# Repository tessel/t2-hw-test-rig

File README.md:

# t2-hw-test-rig

KiCAD design files for test rigs for Technical Machine's Tessel 2

To download [TM's KiCAD library](https://github.com/technicalmachine/tm-kicad-library), containing all the schematic symbols and footprints, run this command:

```
git submodule update --init
```

## Notes

* We use the daily builds of KiCAD (for [Ubuntu](https://code.launchpad.net/~js-reynaud/+archive/ubuntu/ppa-kicad and [OS X](http://www.kicad-pcb.org/display/KICAD/Installing+KiCad#InstallingKiCad-MacOSX) ) and you should too!
* As a general rule, do not assume that schematic, layout, and manufacturig exports were kept abreast on each commit. Do a fresh export (or use tagged releases) if you intend to actually send off gerbers.

### Troubleshooting

**No components rendered in 3D viewer (OS X):** You may need to change the environment variable for the 3D model path. Run this command and reset KiCad; this fix will work for the duration of your logged in session on the computer:

```
launchctl setenv KISYS3DMOD "/Library/Application Support/kicad/packages3d"
```

## Mechanical Model

Our [physical CAD model](https://cad.onshape.com/documents/50a5c011c1d44d7ca5c90fbf) is available on [OnShape](http://onshape.com), a cloud-based 3D CAD system that is free for public projects. It supports export in a variety of formats to other 3D CAD tools.

## License

CC-BY-SA and/or Solderpad at your option except where otherwise noted.

See `license.txt`.

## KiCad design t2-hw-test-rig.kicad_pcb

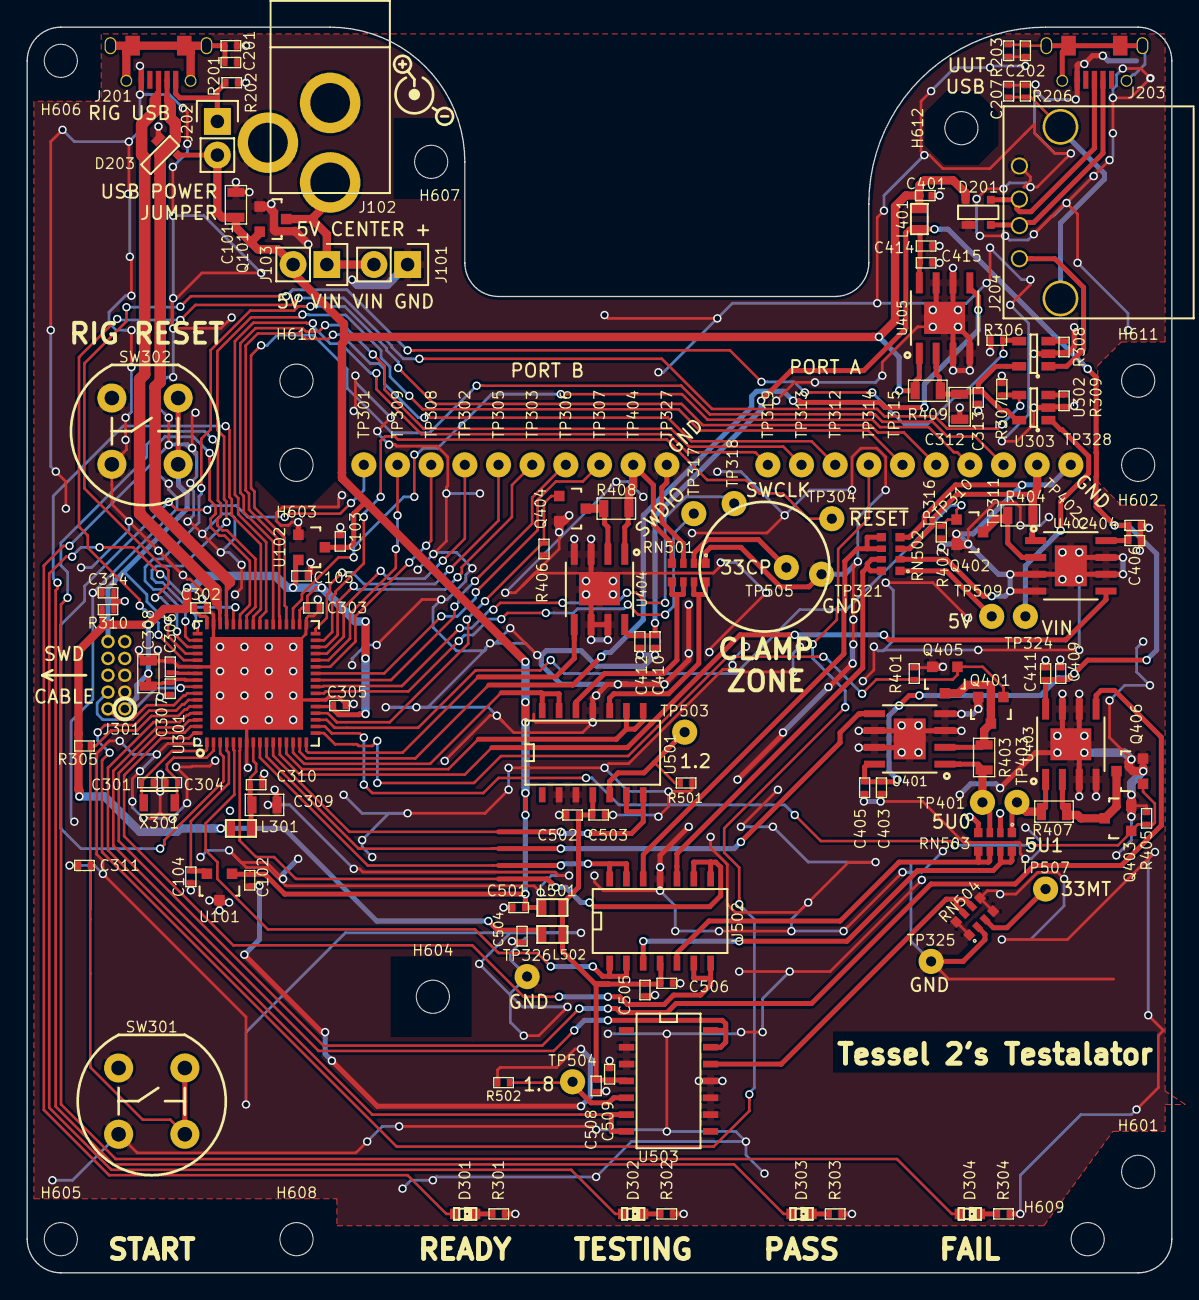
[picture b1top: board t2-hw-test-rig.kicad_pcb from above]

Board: 2 copper layers, 86.4 x 94.0 mm, 157 parts (0 on the bottom side), 95 nets.

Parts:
C101, C308, C309, C312: 10uF; SMD-0805-C
C102, C103, C104, C105, C302, C303, C305, C307, C310, C311, C313, C314, C401, C403, C404, C409, C410, C414, C502, C504, C505, C508: 100nF; SMD-0402-C
C201, C202, C207, C405, C406, C411, C412, C415, C503, C506, C509: 100pF; SMD-0402-C
C301, C304: 10pF; SMD-0402-C
C306: 1uF; SMD-0402-C
C501: 100nF DNP; SMD-0402-C
D201, D203: PRTR5V0U2X,215
D301: BLUE; LED-0603
D302: YELLOW; LED-0603
D303: GREEN; LED-0603
D304: RED; LED-0603
H601, H602, H603, H604, H605, H606, H607, H608, H609, H610, H611, H612: M2.5; MountingHole_2-5mm
J101, J103, J202: CONN_01X02; Pin_Header_Straight_1x02
J102: BARREL_JACK
J201, J203: MICROUSB-TH; Seeed-USB-Micro-320010028
J204: USB_A_TH; USB-A
J301: CONN_02x05, 0.05"; CONN_02x05_0.05in
L301, L401, L502: 10uH; SMD-0603-R
L501: 10uH DNP; SMD-0603-R
Q101: pMOS; SOT-23
Q401, Q402, Q403, Q404: CJ2302; SOT-23
Q405, Q406: CJ2302 DNP; SOT-23
R201, R202, R203, R206: 100kR; SMD-0402-R
R301, R304, R308, R309: 1kR; SMD-0402-R
R302: 330R; SMD-0402-R
R303: 120R; SMD-0402-R
R305, R306, R307, R310, R401, R402, R405, R406, R501, R502: 10kR; SMD-0402-R
R403, R404, R407, R408, R409: 20mR 1%; SMD-0805-R
RN501, RN502, RN503, RN504: ACASA100221002P100; ACAS0612
SW301, SW302: Switch_DPST; SPST-TH
TP301, TP302, TP303, TP304, TP305, TP306, TP307, TP308, TP309, TP310, TP311, TP312, TP313, TP314, TP315, TP316, TP317, TP318, TP319, TP321, TP324, TP325, TP326, TP327, TP328, TP401, TP402, TP403, TP404, TP503, TP504, TP505, TP507, TP509: 0932-0-15-20-77-14-11-0
U101: MAX6102; SOT-23
U102: XC6206P332MR-G; SOT-23
U301: ATSAMD21J18A-MUT; QFN-64-1EP_9x9x0.5-8MILDRC
U302, U303: AAT4610; SOT-23-5
U401, U402, U403, U404, U405: MAX9919FASA+; SOIC-8-N-1EP
U501, U502, U503: TSV324IDT; SOIC-14_N
X301: FC-135

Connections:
5VUSB0_DIV_BUFF: U301.64, U502.6, U502.7
5VUSB1_DIV_BUFF: U301.5, U502.1, U502.2
5V_DIV_BUFF: U301.6, U502.8, U502.9
12_BUFF: U301.11, U501.6, U501.7
18_BUFF: U301.61, U503.6, U503.7
33CP_DIV_BUFF: U301.13, U501.8, U501.9
33MT_DIV_BUFF: U301.62, U503.13, U503.14
33PA_DIV_BUFF: U301.9, U502.13, U502.14
33PB_DIV_BUFF: U301.14, U501.13, U501.14
+3V3: C105.1, C302.1, C303.1, C305.1, C307.1, C308.1, C504.1, J301.1, L301.1, L502.2, R305.2, R310.2, U102.2, U301.21, U301.34, U301.48, U301.56
+5V: C101.1, C102.1, C103.1, C401.1, C501.1, D201.4, D203.4, J103.2, J202.2, L401.2, L501.2, Q101.2, R409.1, U101.1, U102.3, U405.1
/CURRENT/5VUSB0_RS-: Q401.3, Q405.3, R403.2, U401.2
/CURRENT/5VUSB1_RS-: Q403.3, Q406.3, R407.2, U403.2
/CURRENT/33PA_RS-: Q402.3, R404.2, U402.2
/CURRENT/33PB_RS-: Q404.3, R408.2, U404.2
/CURRENT/VCC_CSA: C403.1, C404.1, C405.1, C406.1, C409.1, C410.1, C411.1, C412.1, C414.1, C415.1, L401.1, U401.8, U402.8, U403.8, U404.8, U405.8
/OP AMPS/5VUSB0_DIV: RN503.5, RN503.6, U502.5
/OP AMPS/5VUSB1_DIV: RN503.7, RN503.8, U502.3
/OP AMPS/5V_DIV: RN502.7, RN502.8, U502.10
/OP AMPS/33CP_DIV: RN501.7, RN501.8, U501.10
/OP AMPS/33MT_DIV: RN504.6, RN504.7, U503.12
/OP AMPS/33PA_DIV: RN502.5, RN502.6, U502.12
/OP AMPS/33PB_DIV: RN501.5, RN501.6, U501.12
/OP AMPS/UUT_12: R501.1, TP503.~, U501.5
/OP AMPS/UUT_18: R502.1, TP504.~, U503.5
/OP AMPS/VDD_OPAMPS: C502.1, C503.1, C505.1, C506.1, C508.1, C509.1, L501.1, L502.1, U501.4, U502.4, U503.4
/SAM/FAIL_LED: D304.2, U301.42
/SAM/FAIL_MID: D304.1, R304.2
/SAM/PASS_LED: D303.2, U301.41
/SAM/PASS_MID: D303.1, R303.2
/SAM/PORT_A_G1/TX: TP312.~, U301.37
/SAM/PORT_A_G2/RX: TP313.~, U301.38
/SAM/PORT_A_G3: TP319.~, U301.40
/SAM/PORT_A_MISO: TP315.~, U301.49
/SAM/PORT_A_MOSI: TP314.~, U301.59
/SAM/PORT_A_SCK: TP316.~, U301.50
/SAM/PORT_A_SCL: TP311.~, U301.36
/SAM/PORT_A_SDA: TP310.~, U301.35
/SAM/PORT_B_G1/TX: TP308.~, U301.27
/SAM/PORT_B_G2/RX: TP309.~, U301.28
/SAM/PORT_B_G3: TP301.~, U301.3
/SAM/PORT_B_MISO: TP305.~, U301.32
/SAM/PORT_B_MOSI: TP302.~, U301.29
/SAM/PORT_B_SCK: TP303.~, U301.30
/SAM/PORT_B_SCL: TP307.~, U301.26
/SAM/PORT_B_SDA: TP306.~, U301.25
/SAM/READY_LED: D301.2, U301.43
/SAM/READY_MID: D301.1, R301.2
/SAM/SAM_XTAL32_1: C301.1, U301.1, X301.1
/SAM/SAM_XTAL32_2: C304.1, U301.2, X301.2
/SAM/TEST_IN_PROGRESS_LED: D302.2, U301.44
/SAM/TEST_START_BUTTON: C311.1, R305.1, SW301.2, SW301.4, U301.60
/SAM/TIP_MID: D302.1, R302.2
/SAM/UUT_SWCLK: TP318.~, U301.24
/SAM/UUT_SWDIO: TP317.~, U301.23
/SAM/UUT_VIN: TP324.~, U303.1
/SAM/UUT_~ENABLE~_USB: R306.2, U301.51, U302.4
/SAM/UUT_~ENABLE~_VIN: R307.2, U301.53, U303.4
/SAM/UUT_~RESET: TP304.~, U301.31
/SAM/VDDCORE: C306.1, U301.55
/USB/SAM_USB_SHELL: C201.1, J201.6, J201.7, J201.8, J201.9, J201.10, J201.11, R201.1
/USB/UUT_USB_D+: D201.3, J203.3, J204.3
/USB/UUT_USB_D-: D201.2, J203.2, J204.2
/USB/UUT_USB_PASSTHROUGH_SHELL: C202.1, J203.6, J203.7, J203.8, J203.9, J203.10, J203.11, R203.1
/USB/UUT_USB_SHELL: C207.1, J204.5, J204.6, R206.1
/USB/V_USB_IN: J201.1, J202.1, R202.1
/V_IN: J101.2, J102.1, J103.1, Q101.3
CP_VDDANA: C309.1, C310.1, L301.2, U301.8
GND: C101.2, C102.2, C103.2, C104.2, C105.2, C201.2, C202.2, C207.2, C301.2, C302.2, C303.2, C304.2, C305.2, C306.2, C307.2, C308.2, C309.2, C310.2, C311.2, C312.2, C313.2, C314.2, C401.2, C403.2, C404.2, C405.2, C406.2, C409.2, C410.2, C411.2, C412.2, C414.2, C415.2, C501.2, C502.2, C503.2, C504.2, C505.2, C506.2, C508.2, C509.2, D201.1, D203.1, J101.1, J102.2, J102.3, J201.5, J203.5, J204.4, J301.3, J301.5, Q101.1, Q401.2, Q402.2, Q403.2, Q404.2, Q405.2, Q406.2, R201.2, R202.2, R203.2, R206.2, R301.1, R302.1, R303.1, R304.1, R306.1, R307.1, R308.1, R309.1, R401.2, R402.2, R405.2, R406.2, R501.2, R502.2, RN501.1, RN501.3, RN502.2, RN502.4, RN503.2, RN503.4, RN504.1, RN504.2, RN504.4, RN504.5, RN504.8, SW301.1, SW301.3, SW302.1, SW302.3, TP321.~, TP325.~, TP326.~, TP327.~, TP328.~, U101.3, U102.1, U301.7, U301.22, U301.33, U301.47, U301.54, U301.65, U302.2, U303.2, U401.3, U401.4, U401.6, U401.7, U401.9, U402.3, U402.4, U402.6, U402.7, U402.9, U403.3, U403.4, U403.6, U403.7, U403.9, U404.3, U404.4, U404.6, U404.7, U404.9, U405.3, U405.4, U405.6, U405.7, U405.9, U501.2, U501.3, U501.11, U502.11, U503.2, U503.3, U503.9, U503.10, U503.11
I_PA33: U301.12, U402.5
I_PB33: U301.16, U404.5
I_USB0: U301.10, U401.5
I_USB1: U301.63, U403.5
I_UUT: U301.15, U405.5
unnamed: R308.2, U302.3
unnamed: R309.2, U303.3
PA33_SHORT: Q402.1, R402.1, U301.19
PB33_SHORT: Q404.1, R406.1, U301.20
SAM_USB_D+: D203.2, J201.3, U301.46
SAM_USB_D-: D203.3, J201.2, U301.45
SAM_~RESET: C314.1, J301.10, R310.1, SW302.2, SW302.4, U301.52
SWCLK: J301.4, U301.57
SWDIO: J301.2, U301.58
USB0_SHORT: Q401.1, Q405.1, R401.1, U301.17
USB1_SHORT: Q403.1, Q406.1, R405.1, U301.18
UUT_5V: RN502.1, TP509.~
UUT_5VUSB0: R403.1, RN503.3, TP401.~, U401.1
UUT_5VUSB1: R407.1, RN503.1, TP403.~, U403.1
UUT_5V_UPSTREAM: C312.1, C313.1, R409.2, U302.5, U303.5, U405.2
UUT_33CP: RN501.2, TP505.~
UUT_33MT: RN504.3, TP507.~
UUT_33PA: R404.1, RN502.3, TP402.~, U402.1
UUT_33PB: R408.1, RN501.4, TP404.~, U404.1
UUT_VINUSB: J204.1, U302.1
V_REF: C104.1, U101.2, U301.4

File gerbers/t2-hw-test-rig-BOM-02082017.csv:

,Title,Tessel 2 Test Rig,,,
,Revision,,,,
,Date,Thu 30 Apr 2015,,,
,Generated,Monday, May 30, 2016 'PMt' 12:41:19 PM,
,Company,Technical Machine, Inc.,,
,Comment 1,Copyright 2015,,,
,Comment 2,CC-BY-SA and/or Solderpad at your option ,,,
,Comment 3,,,,
,Comment 4,,,,
,Total Parts,198,,,
,Total Unique Parts,49,,,
,Ref,Qty,Value,Footprint,
,C104 C102 C103 C105 C310 C305 C307 C303 C302 C313 C311 C314 C401 C403 C409 C410 C404 C414 C505 C502 C508 C504 ,22,100nF,SMD-0402,
,C101 C308 C309 C312 ,4,10uF,SMD-0402,
,C201 C207 C202 C405 C411 C412 C406 C415 C503 C506 C509 ,11,100pF,SMD-0402,
,C304 C301 ,2,10pF,SMD-0402,
,C306 ,1,1uF,SMD-0402,
,C501 ,1,100nF DNP,SMD-0402,
,D203 D201 ,2,PRTR5V0U2X,SMD,
,D304 ,1,RED LEDs,LED-0603,
,D302 ,1,YELLOW LEDs,LED-0603,
,D303 ,1,GREENLEDs,LED-0603,
,D301 ,1,BLUELEDs,LED-0603,
,H601 H602 H603 H604 H605 H606 H607 H608 H609 H610 H611 H612 ,12,M2.5,MountingHole_2-5mm,
,J102 ,1,BARREL_JACK,,
,J101 J103 J202 ,3,CONN_01X02,Pin_Header_Straight_1x02,
,J201 J203 ,2,MICROUSB-TH,,
,J204 ,1,USB_A_TH,,
,J301 ,1,CONN_02x05, 0.05 CONN_02x05_0.05in,
,JP101 JP201 ,2,JUMPER,,
,L301 L401 L502 ,3,10uHtm-kicad-lib,SMD-0603-R,
,L501 ,1,10uH DNP,,
,MP601 MP602 MP606 MP607 MP610 MP611 MP614 MP615 MP620 MP625 MP630 ,11,"Mounting Hardware - See Schematic, Mechanical Sheet",,
,MP603 ,1,"Mounting Hardware - See Schematic, Mechanical Sheet",,
,MP605 MP609 MP613 MP617 MP622 MP627 MP632 ,7,"Mounting Hardware - See Schematic, Mechanical Sheet",,
,MP633 ,1,"Mounting Hardware - See Schematic, Mechanical Sheet",,
,MP618 MP623 MP628 ,3,"Mounting Hardware - See Schematic, Mechanical Sheet",,
,MP604 MP608 MP612 MP616 MP621 MP626 MP631 MP619 MP624 MP629 ,10,"Mounting Hardware - See Schematic, Mechanical Sheet",,
,P102 P103 ,2,USB A TO MicroUSB A CABLE,,
,P104 ,1,ETHERNET CABLE,,
,P101 ,1,5VDC POWER,,
,P105 P106 ,2,USB THUMB DRIVE,,
,Q101 ,1,pMOS,SOT-23,
,Q403 Q401 Q402 Q404 ,4,NTR4503NT1G,SOT-23,
,Q405 Q406 ,2,CJ2302 DNP,SOT-23,
,R201 R202 R206 R203 ,4,100k,SMD-0402-R,
,R308 R309 R304 R301 ,4,1k,SMD-0402-R,
,R306 R307 R305 R310 R405 R401 R402 R406 R501 R502 ,10,10k,SMD-0402-R,
,R302 ,1,330,SMD-0402-R,
,R303 ,1,120,SMD-0402-R,
,R407 R403 R404 R408 R409 ,5,20m,SMD-0805-R,
,RN502 RN503 RN501 RN504 ,4,ACASA100221002P100,SMT,http://www.digikey.com/product-detail/en/vishay-beyschlag/AC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
,SW301 SW302 ,2,Switch_DPST,,
,TP321 TP302 TP303 TP305 TP306 TP307 TP308 TP309 TP310 TP311 TP312 TP313 TP317 TP318 TP315 TP316 TP314 TP301 TP304 TP324 TP319 TP325 TP326 TP327 TP328 TP401 TP403 TP404 TP402 TP507 TP505 TP503 TP504 TP509 ,34,0932-0-15-20-77-14-11-0,,
,U101 ,1,MAX6102,SOT-23,
,U102 ,1,XC6206P332MR-G,SOT-23,
,U301 ,1,ATSAMD21J18A-MUT,,
,U302 U303 ,2,AAT4610,SOT-23,
,U403 U401 U402 U404 U405 ,5,MAX9919FASA,SOIC-8,
,U502 U501 U503 ,3,TSV324IDT,SOIC-14,
,X301 ,1,FC-135,SMT,http://www.seeedstudio.com/wiki/images/7/78/306010055.pdf
,,,,,
,,,,,
,,,,,
,,,,,
,BOM made with KICAD_BOM_WIZARD (https://github.com/HashDefineElectronics/KiCad_BOM_Wizard.git),,,,
,Generated Monday, May 30, 2016 'PMt' 12:41:19 PM,,

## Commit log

2015-04-17 added license.txt
2015-04-17 added fp-lib-table to reference tm-kicad-lib
2015-04-17 added gitignore, tm-kicad-lib as submodule
2015-04-17 removed tessel 2 title from readme...
2015-04-17 added the library as submodule
2015-04-17 created project, schematic
2015-04-17 added the SAM and some power-related things
2015-04-17 put at least one of most of the critical components onto the schematic
2015-04-17 added current sense amplifier
2015-04-17 CSA support circuitry
2015-04-17 swapped switcher for an ldo
2015-04-17 saved, closed project
2015-04-17 picked an nmos
2015-04-22 broke out usb and sam to sheets
2015-04-22 added individual sheets for sam, usb, current sense
2015-04-23 ...and now the schematics are in git
2015-04-23 sercoms in place
2015-04-23 analog in, not io
2015-04-24 pin allocations and finally got the opamp in there
2015-04-24 resistor network
2015-04-28 resistor network = RN
2015-04-28 connected analog things, lots of testpoints
2015-04-29 moved a bunch of things around inside the schematics
2015-04-30 schematic check with kevin. misc fixes, mostly on usb
2015-04-30 added single usba to library
2015-05-01 passed schematic review
2015-05-01 incorporated new library components
2015-05-01 sheet info filled in on all sheets
2015-05-01 added testpoint part number, small net naming changes
2015-05-01 annotated
2015-05-01 annotated, netlist
2015-05-04 swapped out new USB_A_TH symbol
2015-05-04 unconventional library hack:moved tm lib above all others so parts come from there first
2015-05-04 updated netlist
2015-05-04 components and footprints
2015-05-04 swapped testpoints
2015-05-04 started pcb file with t2 drills
2015-05-04 added t2-hw-test-rig.kicad_pcb-bak to gitignore
2015-05-05 on to layout! and what an adventure it will be...
2015-05-06 significant progress on placement, sch changes for adc routing
2015-05-06 usb refactor on sch and pcb, mechanical constraints on bcp
2015-05-06 packed parts in
2015-05-06 moved mechanicals to a separate sheet
2015-05-06 consolidated csa power, removed drill map text
2015-05-06 placement "complete"
2015-05-06 drc tweaks
2015-05-07 mostly routed... time to go back and pin mux
2015-05-07 more analog pinswaps
2015-05-07 analog routed!
2015-05-07 now with fewer traces through mounting holes...
2015-05-07 time to move on to the digital side
2015-05-07 port b
2015-05-07 routed
2015-05-07 passes drc except for qfn footprint...
2015-05-07 ready to swap the qfn
2015-05-07 qfn swapped, another mount hole added, passes drc
2015-05-08 moved usb testpoints
2015-05-08 usb port and barrel jack tweaks
2015-05-08 still easier access to usb
2015-05-11 soic-8-1ep footprint fix, moved mount holes for mech clearance
2015-05-11 saved and closed. gerber export
2015-05-11 added idf models for moving to ME CAD
2015-05-11 one more potential mechanical issue removed
2015-05-11 added test rig base plat outline in bfab
2015-05-11 adds base plate laser cut template
2015-05-13 Adds OnShape instructions
    I tried this, it worked, let's document it.
2015-05-13 Update README.md
    Adds direct link.
2015-05-22 opamp rotation
2015-06-01 pulldowns on 1.2, 1.8 and power swap for opamps
2017-02-05 here you go kelsey. the bom should have been added here long ago...
2017-02-10 updates to latest BOM (Seeed made some part swaps)
2017-07-09 Code of Conduct added
